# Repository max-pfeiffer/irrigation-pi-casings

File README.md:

# Irrigation-Pi Casings
3D models for Irrigation-Pi casing that you can print yourself.

## Casings
### Movray
This nice casing was contributed by [@movray](https://github.com/movray).
See it's [documentation](movray/README.md) for versions and printing options.

## Fan and Fan Control
If you want to add a fan to your case, I recommend using a PWM capable fan and the
[PWM Fan Control software from John Parks](https://github.com/folkhack/raspberry-pi-pwm-fan-2). 

For a Raspberry Pi 3 these are good 
[settings for adjusting to the CPU temperature](https://github.com/folkhack/raspberry-pi-pwm-fan-2?tab=readme-ov-file#environment-varibale-reference):
* PWM_FAN_MIN_OFF_TEMP_C=55
* PWM_FAN_MIN_ON_TEMP_C=60
* PWM_FAN_MAX_TEMP_C=70

## Testing Fan Control
Produce stress on the Raspberry Pi:
```shell
stress-ng --cpu 0
```
Watch the CPU temperature in another terminal:
```shell
watch -n 1 vcgencmd measure_temp
```

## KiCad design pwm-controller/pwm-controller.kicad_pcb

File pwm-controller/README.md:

# PWM Controller Board

This is a simple PWM fan controller with optocoupler input.

To keep the design compact and allow single-sided PCB etching, solder pads are used for wiring.

A ZIP archive containing Gerber files is included for PCB fabrication.

## Solder Pads

- J1 → +5V input  
- J2 → FAN + output  
- J3 → PWM signal input  
- J4 → GND  

## Wiring

- Connect J1 directly to Raspberry Pi +5V (Header pin 2 or 4, not a GPIO pin)
- Connect J2 to the positive terminal of the fan
- Connect J3 to Raspberry Pi GPIO18 (Header pin 12)
- Connect J4 to GND

## Notes

The electrical design is relatively robust and supports a wide input range.

- Input voltage: up to 24 V / 1.5 A  
- PWM input signal: 5 V to 12 V compatible  

This design can also be used for other applications.

## Recommended operating limits

| Voltage | Max Current |
|---------|------------|
| 5 V     | 3 A        |
| 9 V     | 2.5 A      |
| 12 V    | 2 A        |
| 15 V    | 1.8 A      |
| 24 V    | 1.5 A      |

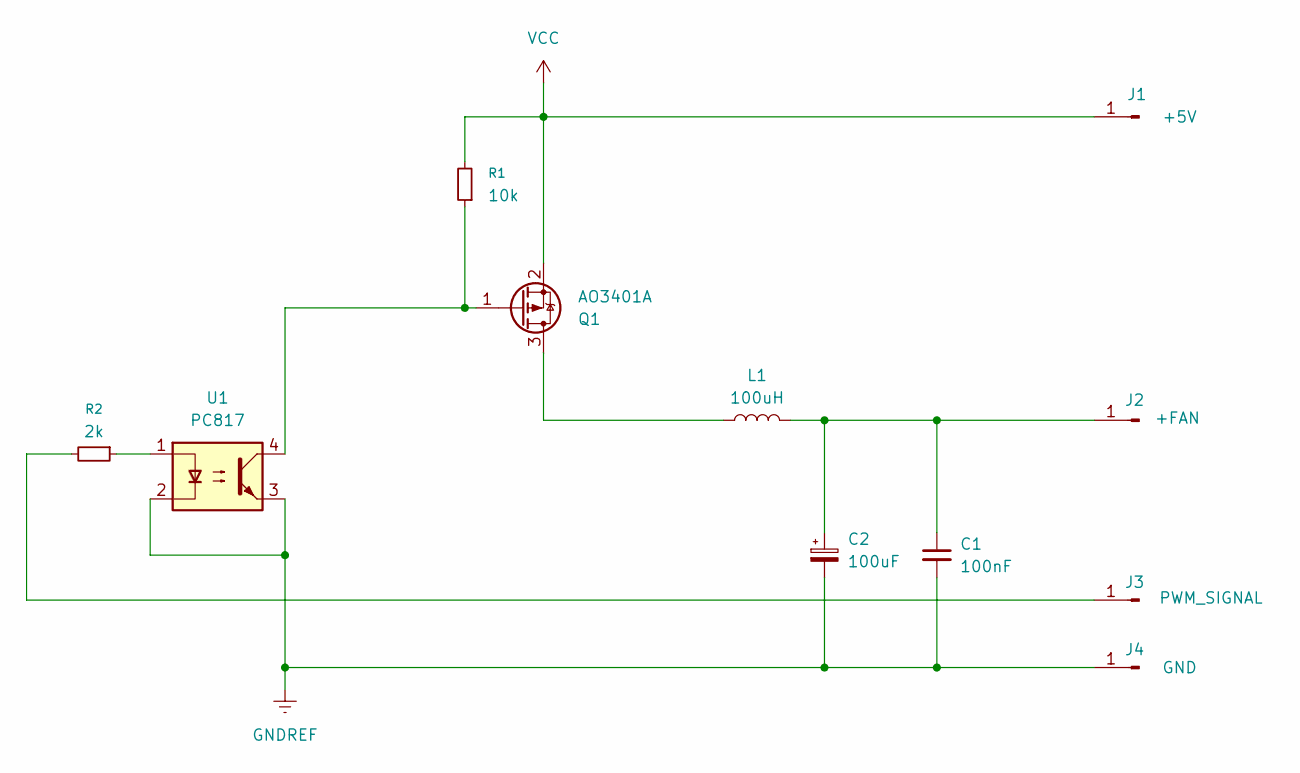
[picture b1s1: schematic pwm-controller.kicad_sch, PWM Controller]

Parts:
C1: 100nF; C_0603_1608Metric
C2: 100uF; CP_Elec_6.3x4.9
J1: +5V; TestPoint_Pad_D1.5mm
J2: +FAN; TestPoint_Pad_D1.5mm
J3: PWM_SIGNAL; TestPoint_Pad_D1.5mm
J4: GND; TestPoint_Pad_D1.5mm
L1: 100uH; L_APV_APH0840
Q1: AO3401A; SOT-23
R1: 10k; R_0603_1608Metric
R2: 2k; R_0603_1608Metric
U1: PC817; DIP-4_W7.62mm_SMDSocket_SmallPads

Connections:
GNDREF: C1.2, C2.2, J4.1, U1.2, U1.3
unnamed: C1.1, C2.1, J2.1, L1.2
unnamed: J3.1, R2.2
unnamed: L1.1, Q1.3 (D)
unnamed: Q1.1 (G), R1.1, U1.4
unnamed: R2.1, U1.1
VCC: J1.1, Q1.2 (S), R1.2

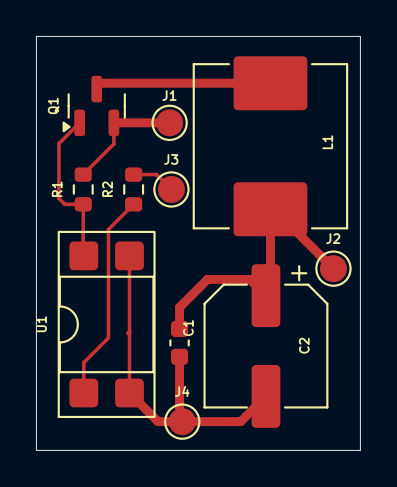
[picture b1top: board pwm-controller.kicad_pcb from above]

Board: 2 copper layers, 18.0 x 23.0 mm, 11 parts (0 on the bottom side), 7 nets.

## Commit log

2026-02-16 Added the great case from Movray
2026-02-16 Added images
2026-02-16 Updated movray readme
2026-03-12 Add docs for fan and fan control
2026-04-03 add pwm controller
2026-04-03 add pwm controller pictures

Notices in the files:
pwm-controller/README.md:
License: MIT
